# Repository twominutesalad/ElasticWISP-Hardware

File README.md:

# ElasticWISP-Hardware
ElasticWISP Power Control Hardware

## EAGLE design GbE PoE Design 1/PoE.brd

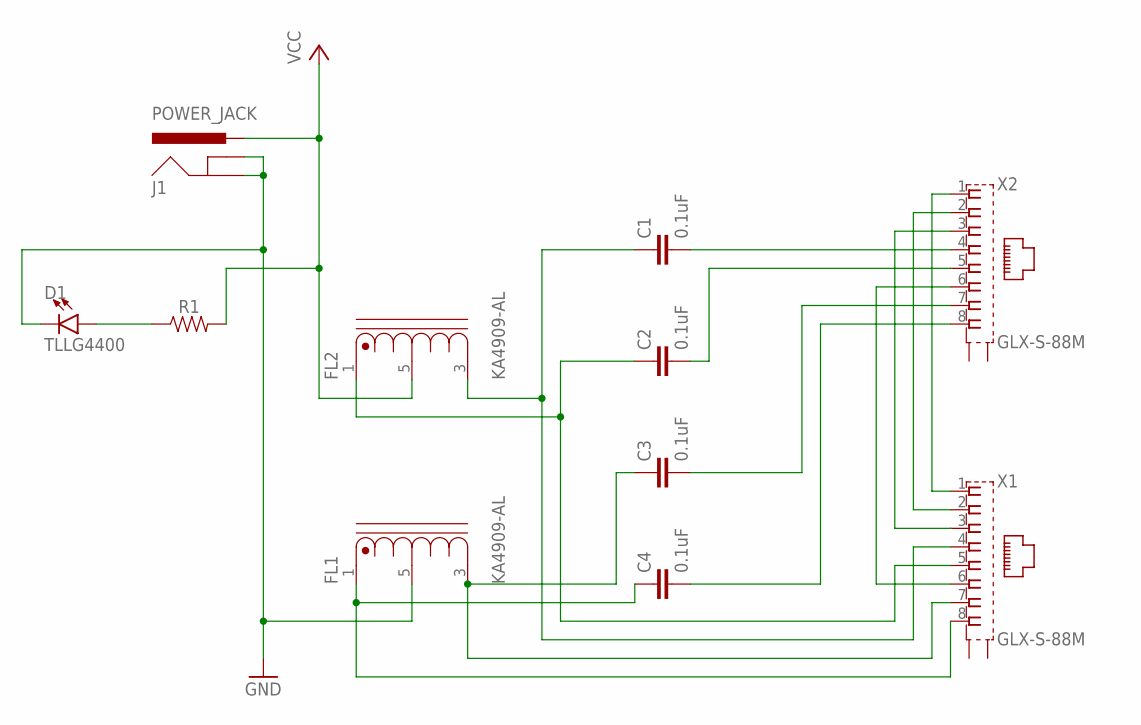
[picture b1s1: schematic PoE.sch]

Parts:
C1, C2, C3, C4: 0.1uF; CAP-PTH-SMALL-KIT
D1: TLLG4400; LED_3MM
FL1, FL2: KA4909-AL; FIL_KA4909-AL
J1: POWER_JACK; POWER_JACK_PTH
R1: AXIAL-0.3
X1, X2: GLX-S-88M

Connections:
GND: D1.K (C), FL1.5, J1.GND, J1.GNDBREAK
unnamed: D1.A, R1.P$1 (1)
unnamed: X1.1, X2.1
unnamed: X1.2, X2.2
unnamed: X1.3, X2.3
unnamed: X1.6, X2.6
unnamed: C1.2, X2.4
unnamed: C2.2, X2.5
unnamed: C3.2, X2.7
unnamed: C4.2, X2.8
unnamed: C1.1, FL2.3, X1.4
unnamed: C2.1, FL2.1, X1.5
unnamed: C4.1, FL1.1, X1.8
unnamed: C3.1, FL1.3, X1.7
VCC: FL2.5, J1.PWR, R1.P$2 (2)

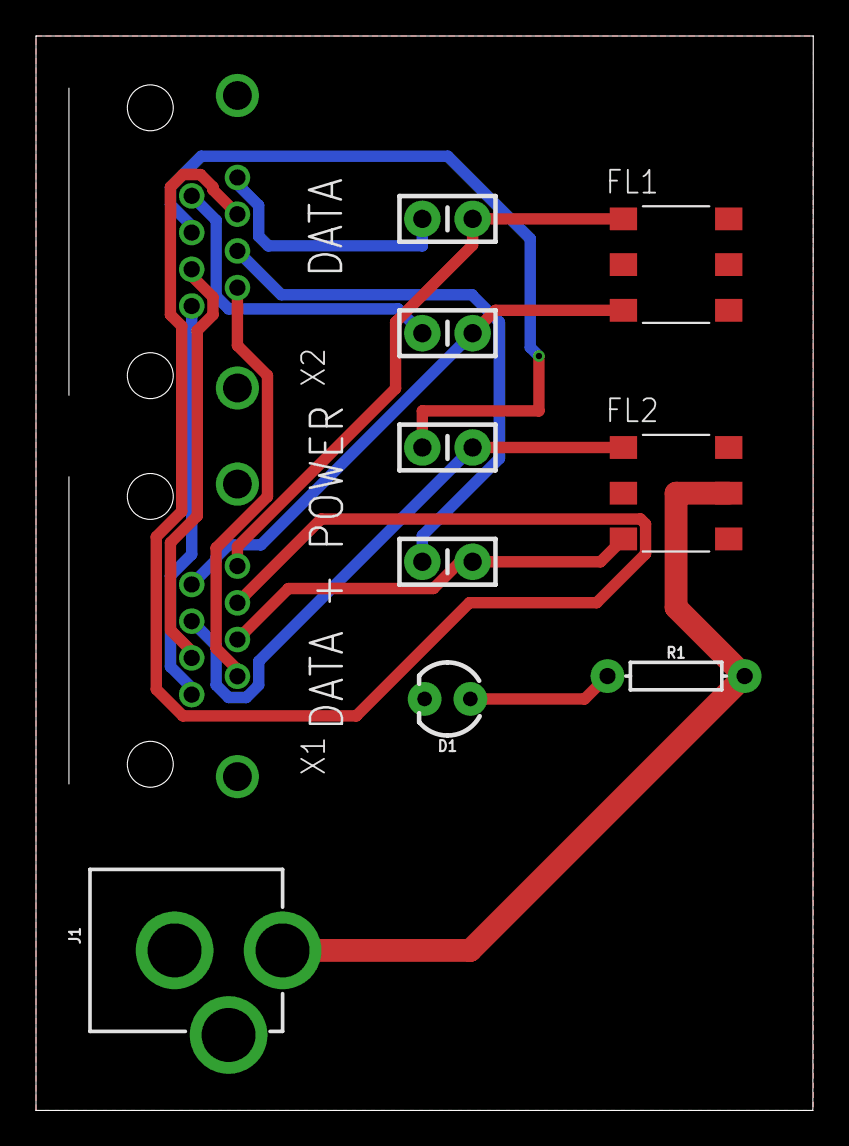
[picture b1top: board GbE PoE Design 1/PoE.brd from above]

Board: 2 copper layers, 43.2 x 59.7 mm, 11 parts (0 on the bottom side), 15 nets.

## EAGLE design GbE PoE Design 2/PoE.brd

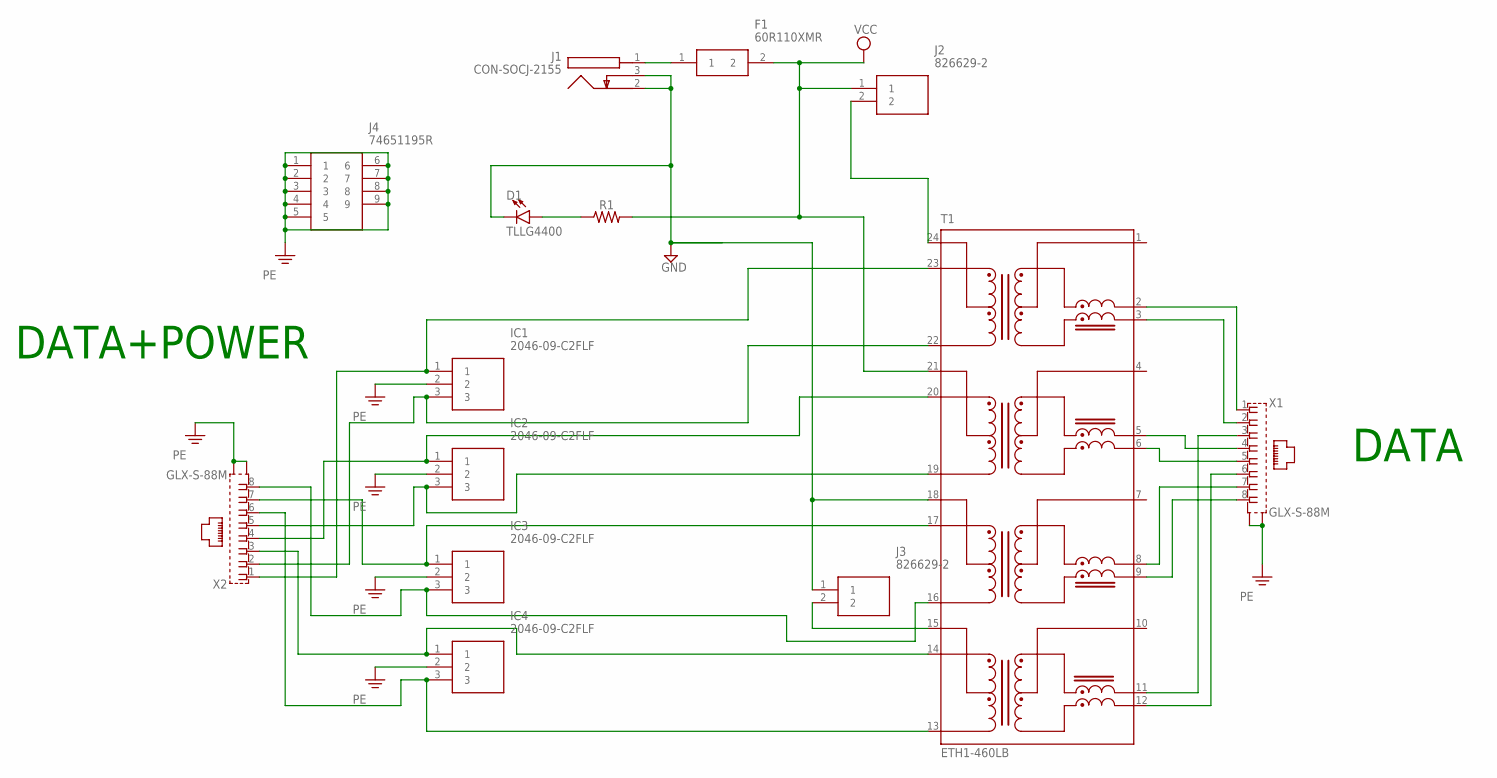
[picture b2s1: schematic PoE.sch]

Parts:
D1: TLLG4400; LED_3MM
F1: 60R110XMR
IC1, IC2, IC3, IC4: 2046-09-C2FLF; 204609C2FLF
J1: CON-SOCJ-2155; CONSOCJ2155
J2, J3: 826629-2; HDRV2W85P0X254_1X2_508X250X950
J4: 74651195R
R1: AXIAL-0.3
T1: ETH1-460LB; XFMR_ETH1-460LB
X1, X2: GLX-S-88M

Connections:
GND: D1.K (C), J1.2, J1.3, J3.1, T1.18 (TXCT_18)
unnamed: D1.A, R1.P$1 (1)
unnamed: T1.2 (TX+_2), X1.1
unnamed: F1.1, J1.1
unnamed: T1.3 (TX-_3), X1.2
unnamed: T1.11 (RX+_11), X1.3
unnamed: T1.12 (RX-_12), X1.6
unnamed: T1.5 (RX+_5), X1.4
unnamed: T1.6 (RX-_6), X1.5
unnamed: T1.8 (TX+_8), X1.7
unnamed: T1.9 (TX-_9), X1.8
unnamed: J2.2, T1.24 (TXCT_24)
unnamed: J3.2, T1.15 (RXCT_15)
unnamed: IC1.1, T1.23 (TX+_23), X2.1
unnamed: IC2.1, T1.20 (RX+_20), X2.4
unnamed: IC2.3, T1.19 (RX-_19), X2.5
unnamed: IC3.1, T1.17 (TX+_17), X2.7
unnamed: IC3.3, T1.16 (TX-_16), X2.8
unnamed: IC4.1, T1.14 (RX+_14), X2.3
unnamed: IC4.3, T1.13 (RX-_13), X2.6
unnamed: IC1.3, T1.22 (TX–_22), X2.2
PE: IC1.2, IC2.2, IC3.2, IC4.2, J4.1, J4.2, J4.3, J4.4, J4.5, J4.6, J4.7, J4.8, J4.9, X1.S1, X1.S2, X2.S1, X2.S2
VCC: F1.2, J2.1, R1.P$2 (2), T1.21 (RXCT_21)

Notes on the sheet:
DATA
DATA+POWER

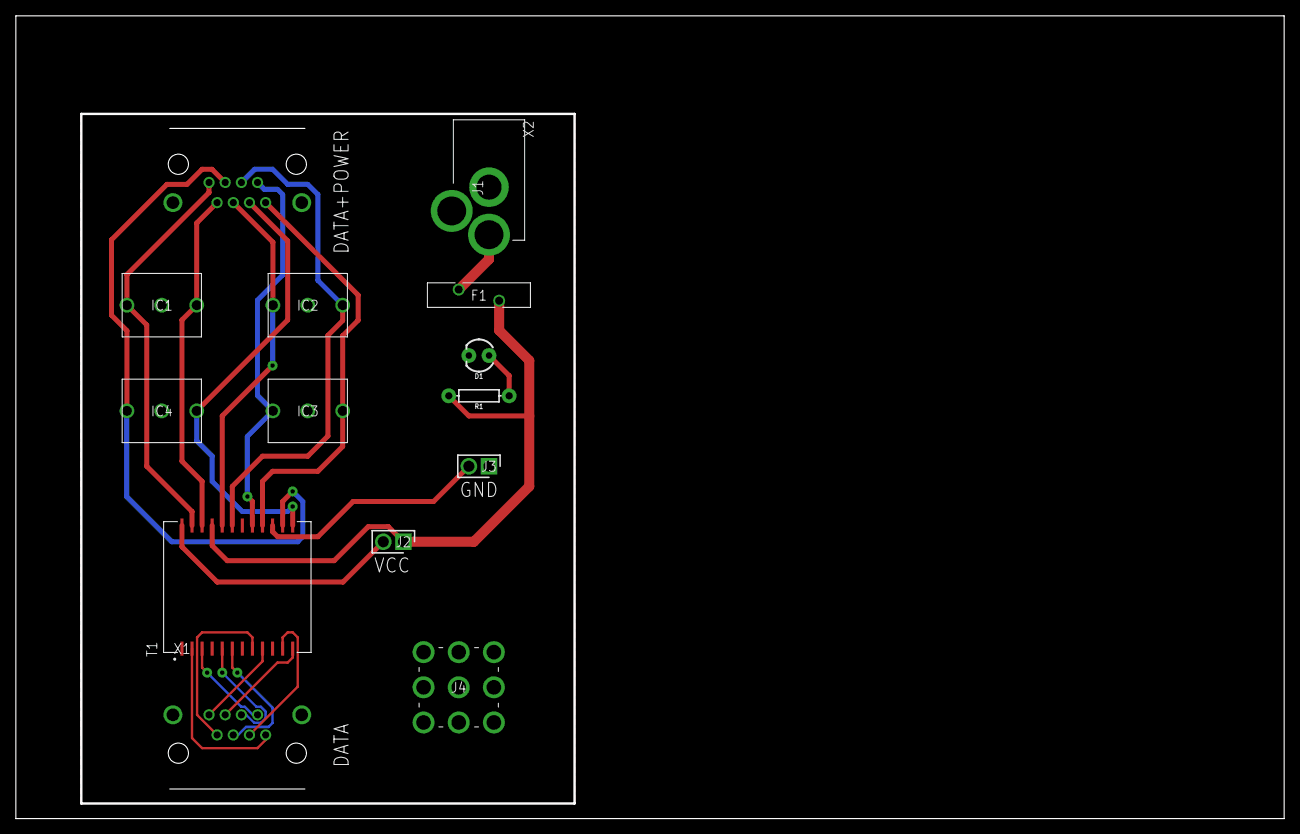
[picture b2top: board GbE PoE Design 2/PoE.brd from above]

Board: 2 copper layers, 160.0 x 101.3 mm, 14 parts (0 on the bottom side), 23 nets.

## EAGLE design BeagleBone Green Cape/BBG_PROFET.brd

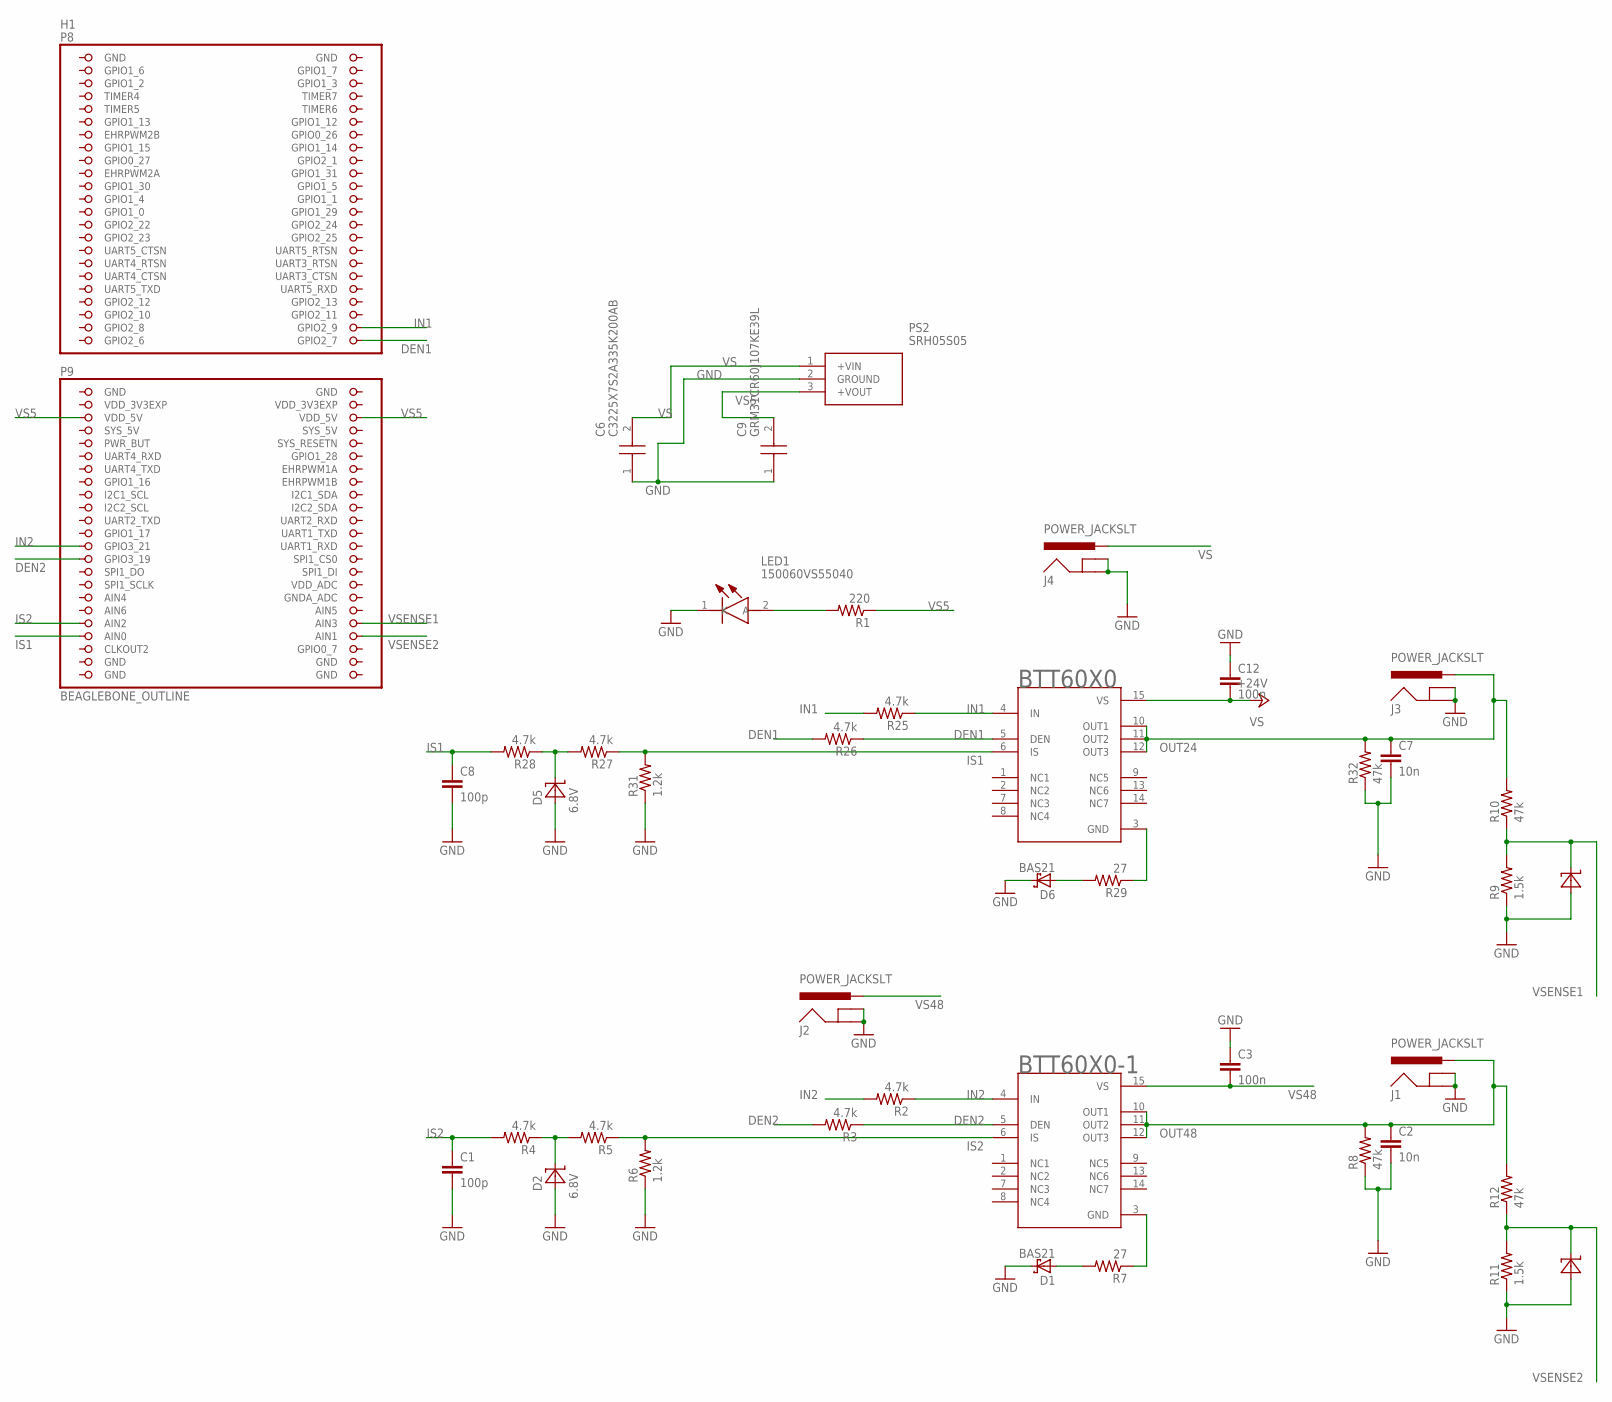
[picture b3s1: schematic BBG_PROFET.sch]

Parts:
BTT60X0, BTT60X0-1: BTT6020-1ERA; SOIC127P600X115-15N-V1
C1, C8: 100p; 0603-CAP
C2, C7: 10n; 0603-CAP
C3, C12: 100n; 0603-CAP
C6: C3225X7S2A335K200AB; CAPC3225X200N
C9: GRM31CR60J107KE39L; CAPC3216X180N
D1, D6: BAS21; SOT23
D2, D5: 6.8V; SMD-PACKAGES_SOD80
D3, D4: 1.8V; SMD-PACKAGES_SOD80
H1: BEAGLEBONE_OUTLINE; BEAGLEBONE_SHIELD
J1, J2, J3, J4: POWER_JACKSLT; POWER_JACK_SLOT
LED1: 150060VS55040; LEDM168X50N
PS2: SRH05S05
R1: 220; 0603-RES
R2, R3, R4, R5, R25, R26, R27, R28: 4.7k; 0603-RES
R6, R31: 1.2k; R1206
R7, R29: 27; 0603-RES
R8, R10, R12, R32: 47k; 0603-RES
R9, R11: 1.5k; 0603-RES

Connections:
DEN1: BTT60X0.5 (DEN), H1.46 (GPIO2_7), R26.1, R26.2
DEN2: BTT60X0-1.5 (DEN), H1.73 (GPIO3_19), R3.1, R3.2
GND: BTT60X0.3 (GND), C1.2, C2.2, C3.1, C6.1, C7.2, C8.2, C9.1, C12.1, D1.3 (C), D2.A, D3.A, D4.A, D5.A, D6.1 (A), D6.3 (C), H1.1 (GND), H1.2 (GND), H1.47 (GND), H1.48 (GND), H1.89 (GND), H1.90 (GND), H1.91 (GND), H1.92 (GND), J1.GND@1 (GNDBREAK), J1.GND@2 (GND), J2.GND@1 (GNDBREAK), J2.GND@2 (GND), J3.GND@1 (GNDBREAK), J3.GND@2 (GND), J4.GND@1 (GNDBREAK), J4.GND@2 (GND), LED1.1 (K), PS2.2 (GROUND), R6.1, R8.1, R9.1, R11.1, R29.1, R29.2, R31.1, R32.1
IN1: BTT60X0.4 (IN), H1.44 (GPIO2_9), R25.1, R25.2
IN2: BTT60X0-1.4 (IN), H1.71 (GPIO3_21), R2.1, R2.2
IS1: BTT60X0.6 (IS), C8.1, D5.K (C), H1.85 (AIN0), R27.1, R27.2, R28.1, R28.2, R31.2
IS2: BTT60X0-1.6 (IS), C1.1, D2.K (C), H1.83 (AIN2), R4.1, R4.2, R5.1, R5.2, R6.2
unnamed: LED1.2 (A), R1.2
unnamed: BTT60X0-1.3 (GND), R7.1
unnamed: D1.1 (A), R7.2
OUT24: BTT60X0.10 (OUT1), BTT60X0.11 (OUT2), BTT60X0.12 (OUT3), C7.1, J3.PWR, R10.2, R32.2
OUT48: BTT60X0-1.10 (OUT1), BTT60X0-1.11 (OUT2), BTT60X0-1.12 (OUT3), C2.1, J1.PWR, R8.2, R12.2
SYS_5V: H1.53 (SYS_5V)
VDD_3V3EXP: H1.49 (VDD_3V3EXP), H1.50 (VDD_3V3EXP)
VS: BTT60X0.15 (VS), C6.2, C12.2, J4.PWR, PS2.1 (+VIN)
VS5: C9.2, H1.51 (VDD_5V), H1.52 (VDD_5V), PS2.3 (+VOUT), R1.1
VS48: BTT60X0-1.15 (VS), C3.2, J2.PWR
VSENSE1: D3.K (C), H1.84 (AIN3), R9.2, R10.1
VSENSE2: D4.K (C), H1.86 (AIN1), R11.2, R12.1

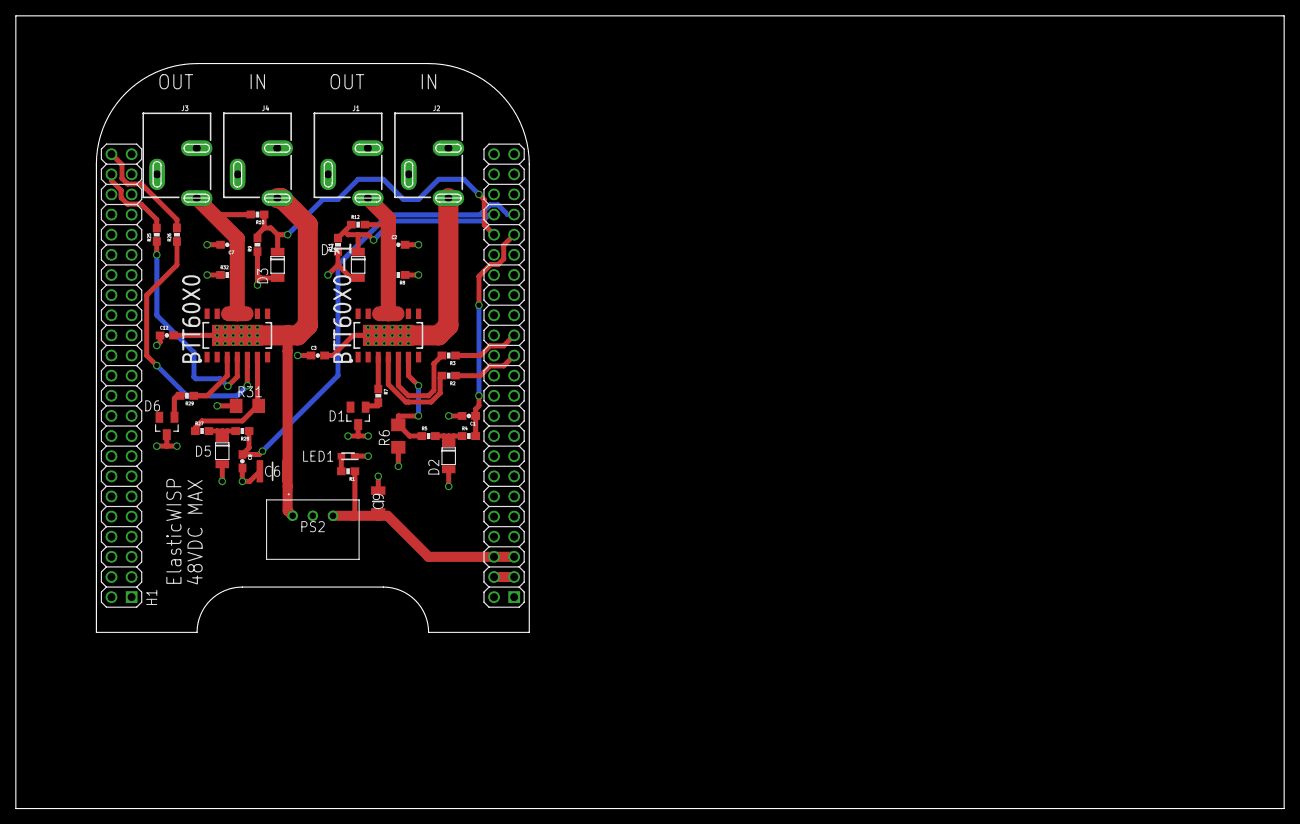
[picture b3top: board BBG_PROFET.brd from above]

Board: 2 copper layers, 160.0 x 100.0 mm, 42 parts (0 on the bottom side), 18 nets.

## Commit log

2020-02-23 Added hardware designs.
    Uploaded hardware designs from ElasticWISP thesis.

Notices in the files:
parts and their libraries:
SparkFun-Connectors: Licensing: Creative Commons ShareAlike 4.0 International - https://creativecommons.org/licenses/by-sa/4.0
